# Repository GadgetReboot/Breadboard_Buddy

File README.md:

# Breadboard_Buddy
PCB with power supplies, audio amp, LEDs, pots and level shifters to make breadboarding easier.

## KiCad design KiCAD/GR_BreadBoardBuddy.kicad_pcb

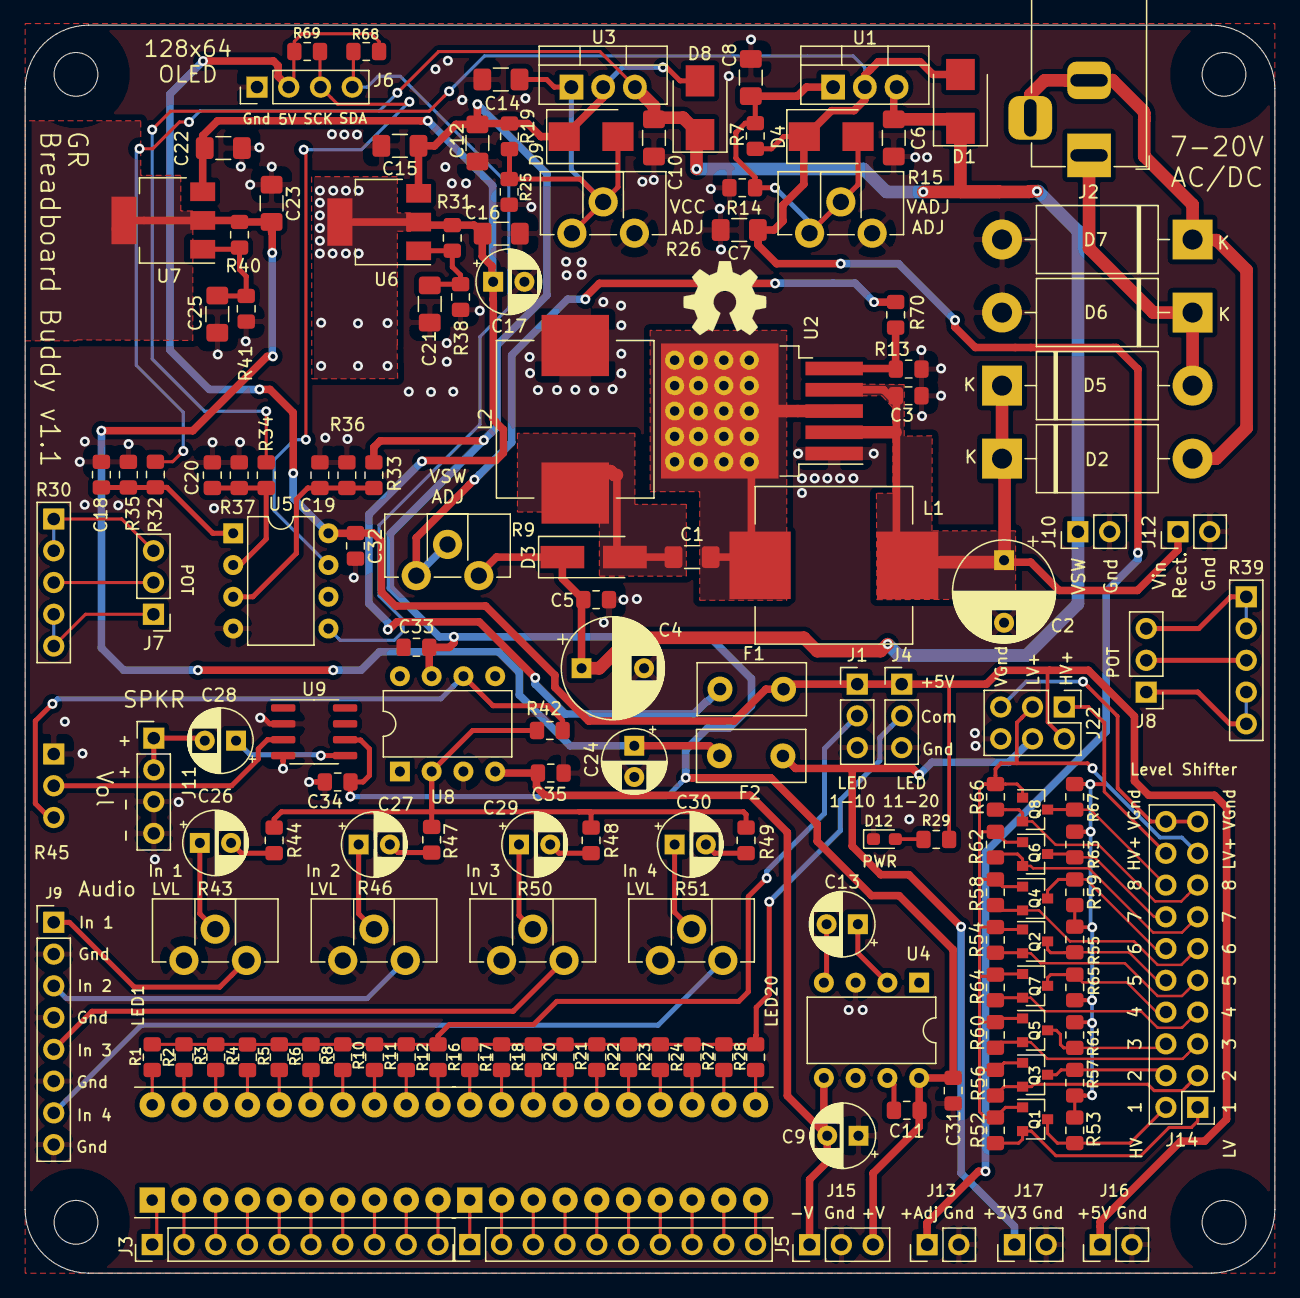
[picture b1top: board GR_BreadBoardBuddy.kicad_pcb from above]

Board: 2 copper layers, 99.9 x 99.8 mm, 156 parts (0 on the bottom side), 113 nets.

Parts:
C1: 22uF; C_1206_3216Metric_Pad1.42x1.75mm_HandSolder
C2: 680uF; CP_Radial_D8.0mm_P5.00mm
C3: 22uF; C_0805_2012Metric_Pad1.15x1.40mm_HandSolder
C4: 22uF; CP_Radial_D8.0mm_P5.00mm
C5: 1uF; C_0805_2012Metric_Pad1.15x1.40mm_HandSolder
C6, C7, C10, C12, C15, C16, C22, C23: 1uF; C_1206_3216Metric_Pad1.42x1.75mm_HandSolder
C8, C14, C21, C25: 10uF; C_1206_3216Metric_Pad1.42x1.75mm_HandSolder
C9, C13, C17, C24, C26, C27, C29, C30: 10uF; CP_Radial_D5.0mm_P2.50mm
C11: 100pF; C_0805_2012Metric_Pad1.15x1.40mm_HandSolder
C18, C19, C20, C31, C32, C33, C34, C35: 100nF; C_0805_2012Metric_Pad1.15x1.40mm_HandSolder
C28: 100uF; CP_Radial_D5.0mm_P2.50mm
D1, D4, D8, D9: 1N4002; D_SMB
D2, D5, D6, D7: 1N5400; D_DO-201AD_P15.24mm_Horizontal
D3: SK35; D_SMA_Handsoldering
D12: LED; LED_0603_1608Metric_Pad1.05x0.95mm_HandSolder
F1, F2: Polyfuse_Small; Fuse_Littelfuse_395Series
J1, J4, J7, J8: Conn_01x03; PinHeader_1x03_P2.54mm_Vertical
J2: Barrel_Jack_MountingPin; DC_BarrelJack
J3, J5: Conn_01x10; PinHeader_1x10_P2.54mm_Vertical
J6, J11: Conn_01x04; PinHeader_1x04_P2.54mm_Vertical
J9: Conn_01x08; PinHeader_1x08_P2.54mm_Vertical
J10: +VSW; PinHeader_1x02_P2.54mm_Vertical
J12: VDC; PinHeader_1x02_P2.54mm_Vertical
J13: +VADJ; PinHeader_1x02_P2.54mm_Vertical
J14: Conn_02x10_Odd_Even; PinHeader_2x10_P2.54mm_Vertical
J15: +/-VCC; PinHeader_1x03_P2.54mm_Vertical
J16: +5V; PinHeader_1x02_P2.54mm_Vertical
J17: +3V3; PinHeader_1x02_P2.54mm_Vertical
J22: Conn_02x03_Odd_Even; PinHeader_2x03_P2.54mm_Vertical
L1, L2: 33uH; L_Wuerth_WE-PD-Typ-LS_Handsoldering
LED_Array1, LED_Array2: HDSP-4830_2; LED_Array_10
Q1, Q2, Q3, Q4, Q5, Q6, Q7, Q8: BSS138; SOT-23
R1, R2, R3, R4, R5, R6, R8, R10, R11, R12, R16, R17, R18, R20, R21, R22, R23, R24, R27, R28: 2K; R_0805_2012Metric_Pad1.15x1.40mm_HandSolder
R7, R19, R31, R40: 120r; R_0805_2012Metric_Pad1.15x1.40mm_HandSolder
R9, R43, R46, R50, R51: 10K; Potentiometer_ACP_CA9-H2,5_Horizontal
R13, R29: 1K; R_0805_2012Metric_Pad1.15x1.40mm_HandSolder
R14, R25: 2K7; R_0805_2012Metric_Pad1.15x1.40mm_HandSolder
R15: 5K; Potentiometer_ACP_CA9-H2,5_Horizontal
R26: 1K; Potentiometer_ACP_CA9-H2,5_Horizontal
R30, R39: R_POT_US; Pot_1x05_P2.54mm_H1.0mm
R32, R34: 56K; R_0805_2012Metric_Pad1.15x1.40mm_HandSolder
R33: 20K; R_0805_2012Metric_Pad1.15x1.40mm_HandSolder
R35, R36, R37, R42, R44, R47, R48, R49, R52, R53, R54, R55, R56, R57, R58, R59, R60, R61, R62, R63, R64, R65, R66, R67, R68, R69: 10K; R_0805_2012Metric_Pad1.15x1.40mm_HandSolder
R38: 360r; R_0805_2012Metric_Pad1.15x1.40mm_HandSolder
R41: 200r; R_0805_2012Metric_Pad1.15x1.40mm_HandSolder
R45: R_POT_US; PinHeader_1x03_P2.54mm_Vertical_NoSilk_H1.0mm
R70: 7K5; R_0805_2012Metric_Pad1.15x1.40mm_HandSolder
U1, U3: LM317; TO-220-3_Vertical
U2: XL6009; TO-263-5_TabPin6_Vias
U4: ICL7660; DIP-8_W7.62mm
U5: ATtiny85-20PU; DIP-8_W7.62mm
U6, U7: LM1117-ADJ; SOT-223-3_TabPin2
U8: TL071; DIP-8_W7.62mm
U9: LM386; SOIC-8_3.9x4.9mm_P1.27mm

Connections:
+3V3: F2.1, J17.1, J22.4
+5V: C32.1, F1.1, J1.1, J4.1, J6.2, J16.1, J22.2, R29.1, R68.2, R69.2, U5.8
/+VADJ: C7.1, D1.2, D4.1, J13.1, R7.2, R34.2, U1.2
/+VCC: C11.1, C12.1, C15.1, C31.1, C33.2, C34.2, D8.2, D9.1, J15.3, R19.2, R33.2, U3.2, U4.8, U6.3, U8.7, U9.6
/+VSW: C4.1, C5.1, C6.1, C10.1, D1.1, D3.1, D8.1, J10.1, R9.3, R32.2, U1.3, U3.3
/-VCC: C9.2, C35.2, J15.1, U4.5, U8.4
/SCK: J6.3, R69.1, U5.7
/SDA: J6.4, R68.1, U5.5
/VGND: J14.19, J14.20, J22.5
/VH1: J14.2, Q1.3, R53.1
/VH2: J14.4, Q3.3, R57.1
/VH3: J14.6, Q5.3, R61.1
/VH4: J14.8, Q7.3, R65.1
/VH5: J14.10, Q2.3, R55.1
/VH6: J14.12, Q4.3, R59.1
/VH7: J14.14, Q6.3, R63.1
/VH8: J14.16, Q8.3, R67.1
/VHigh: J14.18, J22.1, R53.2, R55.2, R57.2, R59.2, R61.2, R63.2, R65.2, R67.2
/VL1: J14.1, Q1.2, R52.1
/VL2: J14.3, Q3.2, R56.1
/VL3: J14.5, Q5.2, R60.1
/VL4: J14.7, Q7.2, R64.1
/VL5: J14.9, Q2.2, R54.1
/VL6: J14.11, Q4.2, R58.1
/VL7: J14.13, Q6.2, R62.1
/VL8: J14.15, Q8.2, R66.1
/VLow: J14.17, J22.3, Q1.1, Q2.1, Q3.1, Q4.1, Q5.1, Q6.1, Q7.1, Q8.1, R52.2, R54.2, R56.2, R58.2, R60.2, R62.2, R64.2, R66.2
GNDREF: C2.2, C3.2, C4.2, C5.2, C6.2, C7.2, C8.2, C9.1, C10.2, C12.2, C14.2, C15.2, C16.2, C17.2, C18.2, C19.2, C20.2, C21.2, C22.2, C23.2, C24.2, C25.2, C31.2, C32.2, C33.1, C34.1, C35.1, D6.2, D7.2, D12.1, J1.3, J4.3, J6.1, J9.2, J9.4, J9.6, J9.8, J10.2, J11.3, J11.4, J12.2, J13.2, J15.2, J16.2, J17.2, J22.6, L2.2, R13.1, R14.1, R15.3, R25.1, R26.3, R35.1, R36.1, R37.1, R38.1, R41.1, R43.1, R45.1, R46.1, R50.1, R51.1, U2.1, U4.3, U5.4, U8.3, U9.2, U9.4
unnamed: C1.1, D3.2, L2.1
unnamed: C1.2, L1.2, U2.3, U2.6
unnamed: C2.1, C3.1, D2.1, D5.1, J12.1, L1.1, U2.2, U2.4
unnamed: C8.1, D4.2, R7.1, R14.2, R15.1, R15.2, U1.1
unnamed: C11.2, U4.7
unnamed: C13.1, U4.2
unnamed: C13.2, U4.4
unnamed: C14.1, D9.2, R19.1, R25.2, R26.1, R26.2, U3.1
unnamed: C16.1, C17.1, C22.1, F1.2, R31.2, U6.2, U7.3
unnamed: C18.1, R32.1, R35.2, U5.1
unnamed: C19.1, R33.1, R36.2, U5.3
unnamed: C20.1, R34.1, R37.2, U5.2
unnamed: C21.1, R31.1, R38.2, U6.1
unnamed: C23.1, C24.1, F2.2, R40.2, U7.2
unnamed: C25.1, R40.1, R41.2, U7.1
unnamed: C26.1, R43.2
unnamed: C26.2, R44.2
unnamed: C27.1, R46.2
unnamed: C27.2, R47.2
unnamed: C28.1, U9.5
unnamed: C28.2, J11.1, J11.2
unnamed: C29.1, R50.2
unnamed: C29.2, R48.2
unnamed: C30.1, R51.2
unnamed: C30.2, R49.2
unnamed: D2.2, D7.1, J2.2, J2.MP
unnamed: D5.2, D6.1, J2.1
unnamed: D12.2, R29.2
unnamed: J1.2, R1.1, R2.1, R3.1, R4.1, R5.1, R6.1, R8.1, R10.1, R11.1, R12.1
unnamed: J3.1, LED_Array1.1
unnamed: J3.2, LED_Array1.2
unnamed: J3.3, LED_Array1.3
unnamed: J3.4, LED_Array1.4
unnamed: J3.5, LED_Array1.5
unnamed: J3.6, LED_Array1.6
unnamed: J3.7, LED_Array1.7
unnamed: J3.8, LED_Array1.8
unnamed: J3.9, LED_Array1.9
unnamed: J3.10, LED_Array1.10
unnamed: J4.2, R16.1, R17.1, R18.1, R20.1, R21.1, R22.1, R23.1, R24.1, R27.1, R28.1
unnamed: J5.1, LED_Array2.1
unnamed: J5.2, LED_Array2.2
unnamed: J5.3, LED_Array2.3
unnamed: J5.4, LED_Array2.4
unnamed: J5.5, LED_Array2.5
unnamed: J5.6, LED_Array2.6
unnamed: J5.7, LED_Array2.7
unnamed: J5.8, LED_Array2.8
unnamed: J5.9, LED_Array2.9
unnamed: J5.10, LED_Array2.10
unnamed: J7.1, R30.3
unnamed: J7.2, R30.2
unnamed: J7.3, R30.1
unnamed: J8.1, R39.3
unnamed: J8.2, R39.2
unnamed: J8.3, R39.1
unnamed: J9.1, R43.3
unnamed: J9.3, R46.3
unnamed: J9.5, R50.3
unnamed: J9.7, R51.3
unnamed: LED_Array1.11, R12.2
unnamed: LED_Array1.12, R11.2
unnamed: LED_Array1.13, R10.2
unnamed: LED_Array1.14, R8.2
unnamed: LED_Array1.15, R6.2
unnamed: LED_Array1.16, R5.2
unnamed: LED_Array1.17, R4.2
unnamed: LED_Array1.18, R3.2
unnamed: LED_Array1.19, R2.2
unnamed: LED_Array1.20, R1.2
unnamed: LED_Array2.11, R28.2
unnamed: LED_Array2.12, R27.2
unnamed: LED_Array2.13, R24.2
unnamed: LED_Array2.14, R23.2
unnamed: LED_Array2.15, R22.2
unnamed: LED_Array2.16, R21.2
unnamed: LED_Array2.17, R20.2
unnamed: LED_Array2.18, R18.2
unnamed: LED_Array2.19, R17.2
unnamed: LED_Array2.20, R16.2
unnamed: R13.2, R70.1, U2.5
unnamed: R42.1, R45.3, U8.6
unnamed: R42.2, R44.1, R47.1, R48.1, R49.1, U8.2
unnamed: R45.2, U9.3
unnamed: R9.1, R9.2, R70.2
